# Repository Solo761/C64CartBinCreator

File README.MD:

# C64 Cartridge Creator tool

This is small utility written in Java (1.8) for converting C64 prg files to BIN files for burning to (E)EPROM chips, of up to 64 kB.

## More info

You can choose from three types of cartidges, *Magic Desk*, *Hucky* and *Inverted Hucky*. You can also choose between two types of C64 loaders for these files. First one is loader from Frank Buß' prg2crt python script that can be found [here](http://www.frank-buss.de/c64/prg2crt/index.html), used here with his permission, and the other is loader from C64 tool 152blks.prg that can be used on real C64 (or emulator like Vice) to convert prg files from PRG to *Hucky* type bin files. Now it can be used to also make *Magic Desk* and *Inverted Hucky* type bin files.

From what I've tested both loaders work fine, main difference is that prg2crt loader takes less space, but it doesn't "hide" loading and processing from the screen. 152blks loader uses more space for itself, but it blacks the screen so while it loads from the cartridge you don't see anything happening. So to each to his own.

Beside bin files it can also create CRT for use (or testing) with emulators. With exception of *Hucky* cartridges which aren't supported in CRT file format (at least yet). If you choose combination of Hucky and CRT files tool will warn you about this and ask if you want to abort or continue to create *Inverted Hucky* (also called *RGCD*) CRT instead. 
Basically, difference between *Hucky* and *Inverted Hucky* is order of memory banks, everything else is the same.

## GUI Usage

Basically just start jar file. Either from command line

`java -jar cartCreator.jar`

or just double click jar file from windows, on my PC (Win 10) it automatically starts the tool.

Tool should also work on other OS' that have Java, I tried to avoid OS specific stuff in the code.

## Command Line usage

Tool also supports command line usage, enter 

`java -jar cartCreator.jar -h`

in command line to see help

- Parameters:
	-  **-i \<input file\>** -prg file to convert`
	-  **-t \<cartidge type\>**	- which cartridge type to convert to
		- Cartridge types:
			- **h** - Hucky 64kB
			- **ih** - inverted Hucky 64kB
			- **md** - MagicDesk 64kB
	- **-l \<loader type\>** - which loader to use
		 - Loader types:
			- **a** - prg2crt loader from Frank Buß' python script
			- **b** - 152Blks loader

- Semioptional (you need at least one of them):
	- **-c** - convert to emulation cartridge format (CRT)
	- **-b** - convert to bin file for burning to (E)EPROM

- Optional:
	 - **-o \<output file\>** - output file to save converted file to, if it differs from input file
	- **-h** - help

Order of parameters is not important.

For example:

Convert prg to inverted hucky bin file using "a" variant loader

`java -jar cartConv.jar -i BubbleBobble.prg -t ih -b -l a`

Convert prg to MagicDesk CRT file for use in emulator (e.g. Vice) and bin file using "b" variant loader

`java -jar cartConv.jar -i BubbleBobble.prg -o BubbleBobbleEmu.crt -t md -l b -c -b`

## Additional stuff

In folder *EagleSchematics* are two PCB schematics and designs that can be opened with Eagle PCB, one for MagicDesk compatible cartridge and the other for Hucky/Inverted Hucky cartridge (how you solder three bridges on PCB selects if it's going to work as Inverted Hucky or normal Hucky board.

There are also gerber files for both of them if you want to order them from some PCB manufacturer. If they don't require some special settings these should do, if not you can load schematics/design files to Eagle and make gerber files with their settings.

So far they're untested, I've made one Hucky board DIY with above schematics and it works. I also have both boards made from above gerber files, but so far haven't tried them, I've been busy making this tool :).

MagicDesk board should support up to **256 kB (E)EPROM chips**, but can create only up to 64 kB images. Or more simply said, it needs to fit in C64 RAM, basically any game that could be ran from the tape. 
While it could create BIN/CRT files from bigger PRG files they wouldn't be able to start as they wouldn't fit in C64 RAM.
But you can use [Magic Desk Compatible Cartridge Generator tool](http://csdb.dk/release/?id=132937) from C64 Scene Database to create multi game/application cartridges to fill those 256 kB. My goal for this was to make one cartridge - one game so I didn't dig deeper into it.

**Hucky/Inverted Hucky** 

**MagicDesk**

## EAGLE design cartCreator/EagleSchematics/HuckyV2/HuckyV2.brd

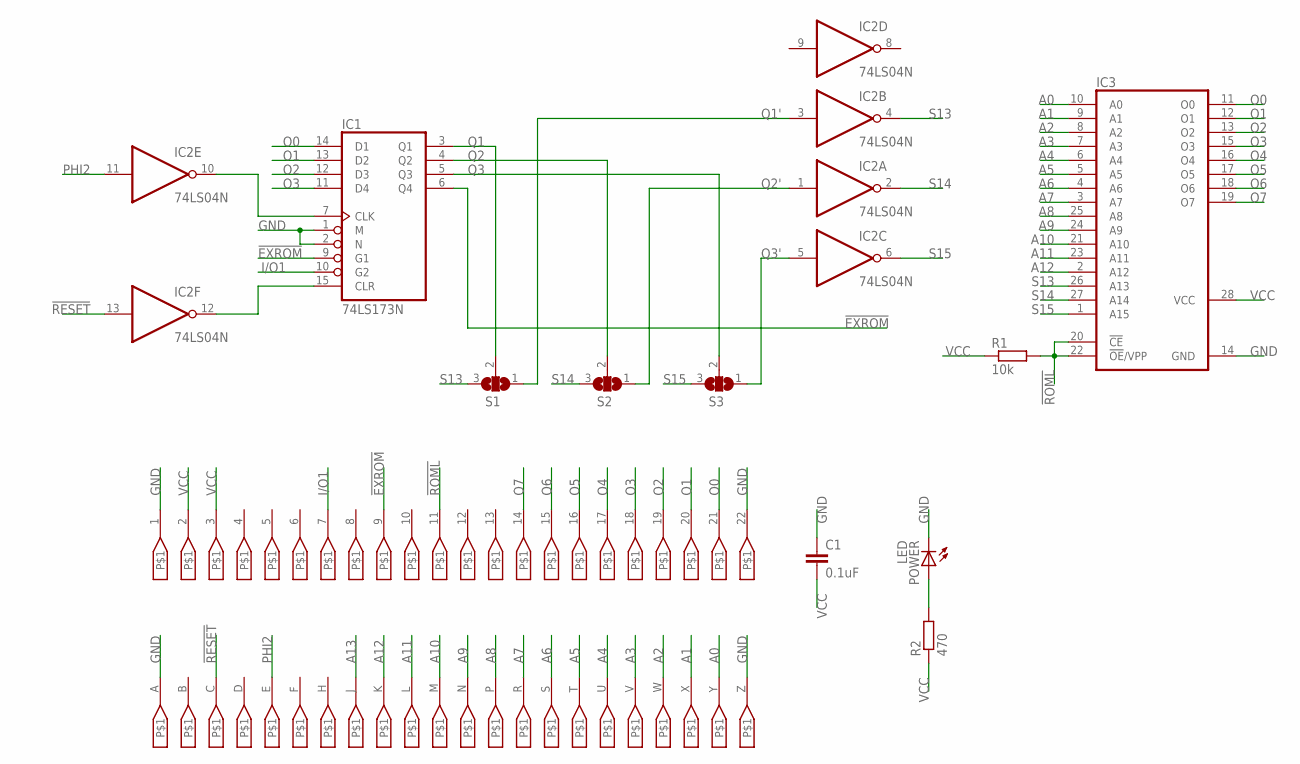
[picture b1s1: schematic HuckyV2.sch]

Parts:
C1: 0.1uF; C050-24X044_SP
IC1: 74LS173N; DIL16
IC2: 74LS04N; DIL14
IC3: 27C512D; DIL28-6
POWER: LED; LED3MM_SMALLER_DRILL
R1: 10k; 0207/10_SP
R2: 470; 0207/10_SP
S1, S2, S3: SJ2W_NUMBERED; SJ_2_NUM
U$1: C64_EXPANSION_FINGERS_PIN8X1.9; C64_EXPANSION_FINGERS_THINNER

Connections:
!EXROM: IC1.6 (Q4), IC1.9 (G1), U$1.9
!RESET: IC2.13 (I), U$1.C
!ROML: IC3.20 (!CE), IC3.22 (!OE!/VPP), R1.2, U$1.11
A0: IC3.10 (A0), U$1.Y
A1: IC3.9 (A1), U$1.X
A2: IC3.8 (A2), U$1.W
A3: IC3.7 (A3), U$1.V
A4: IC3.6 (A4), U$1.U
A5: IC3.5 (A5), U$1.T
A6: IC3.4 (A6), U$1.S
A7: IC3.3 (A7), U$1.R
A8: IC3.25 (A8), U$1.P
A9: IC3.24 (A9), U$1.N
A10: IC3.21 (A10), U$1.M
A11: IC3.23 (A11), U$1.L
A12: IC3.2 (A12), U$1.K
A13: U$1.J
GND: C1.1, IC1.1 (M), IC1.2 (N), IC1.8 (GND), IC2.7 (GND), IC3.14 (GND), POWER.K (C), U$1.1, U$1.22, U$1.A, U$1.Z
I/O1: IC1.10 (G2), U$1.7
unnamed: IC1.7 (CLK), IC2.10 (O)
unnamed: IC1.15 (CLR), IC2.12 (O)
unnamed: POWER.A, R2.2
O0: IC1.14 (D1), IC3.11 (O0), U$1.21
O1: IC1.13 (D2), IC3.12 (O1), U$1.20
O2: IC1.12 (D3), IC3.13 (O2), U$1.19
O3: IC1.11 (D4), IC3.15 (O3), U$1.18
O4: IC3.16 (O4), U$1.17
O5: IC3.17 (O5), U$1.16
O6: IC3.18 (O6), U$1.15
O7: IC3.19 (O7), U$1.14
PHI2: IC2.11 (I), U$1.E
Q1: IC1.3 (Q1), S1.2
Q1': IC2.3 (I), S1.1
Q2: IC1.4 (Q2), S2.2
Q2': IC2.1 (I), S2.1
Q3: IC1.5 (Q3), S3.2
Q3': IC2.5 (I), S3.1
S13: IC2.4 (O), IC3.26 (A13), S1.3
S14: IC2.2 (O), IC3.27 (A14), S2.3
S15: IC2.6 (O), IC3.1 (A15), S3.3
VCC: C1.2, IC1.16 (VCC), IC2.14 (VCC), IC3.28 (VCC), R1.1, R2.1, U$1.2, U$1.3

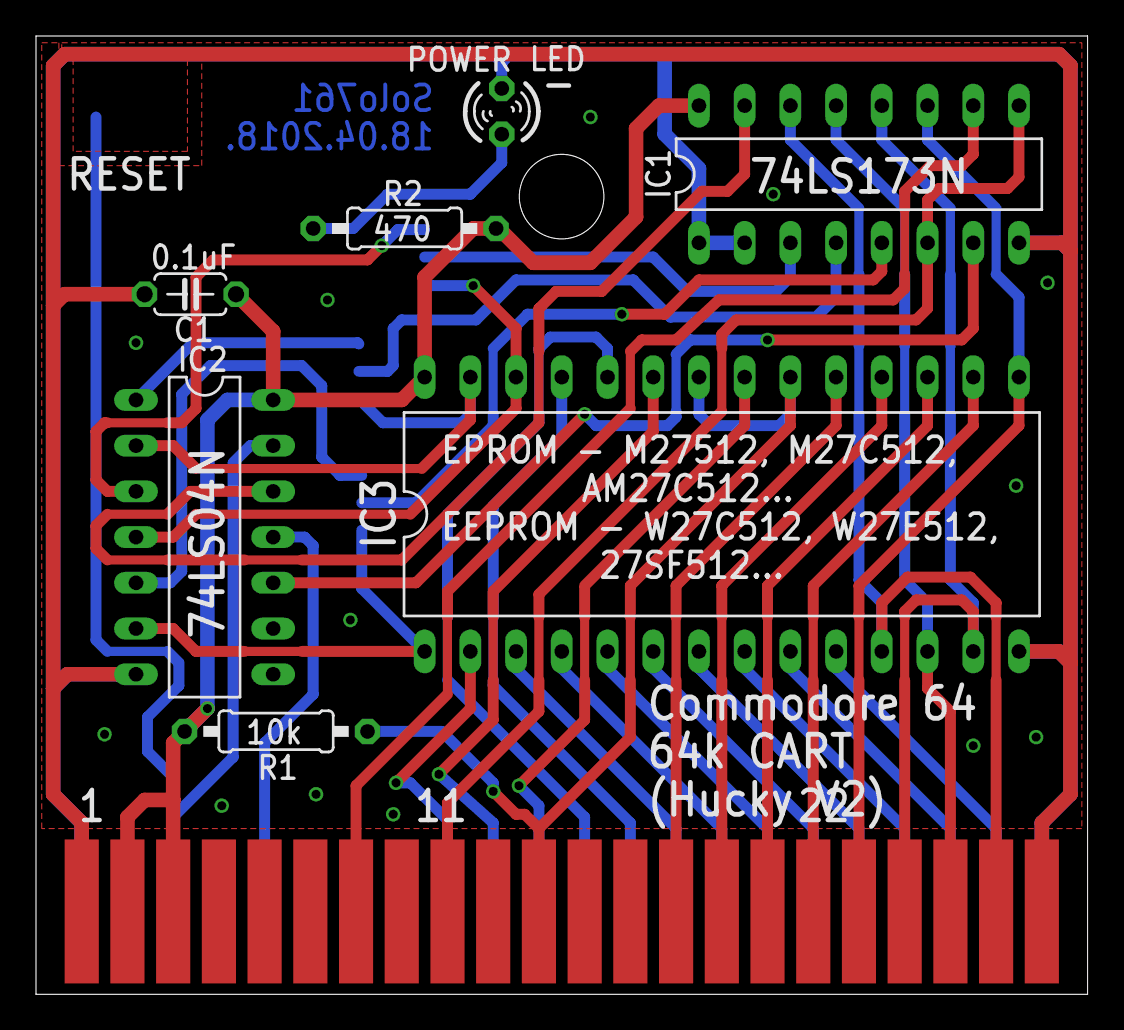
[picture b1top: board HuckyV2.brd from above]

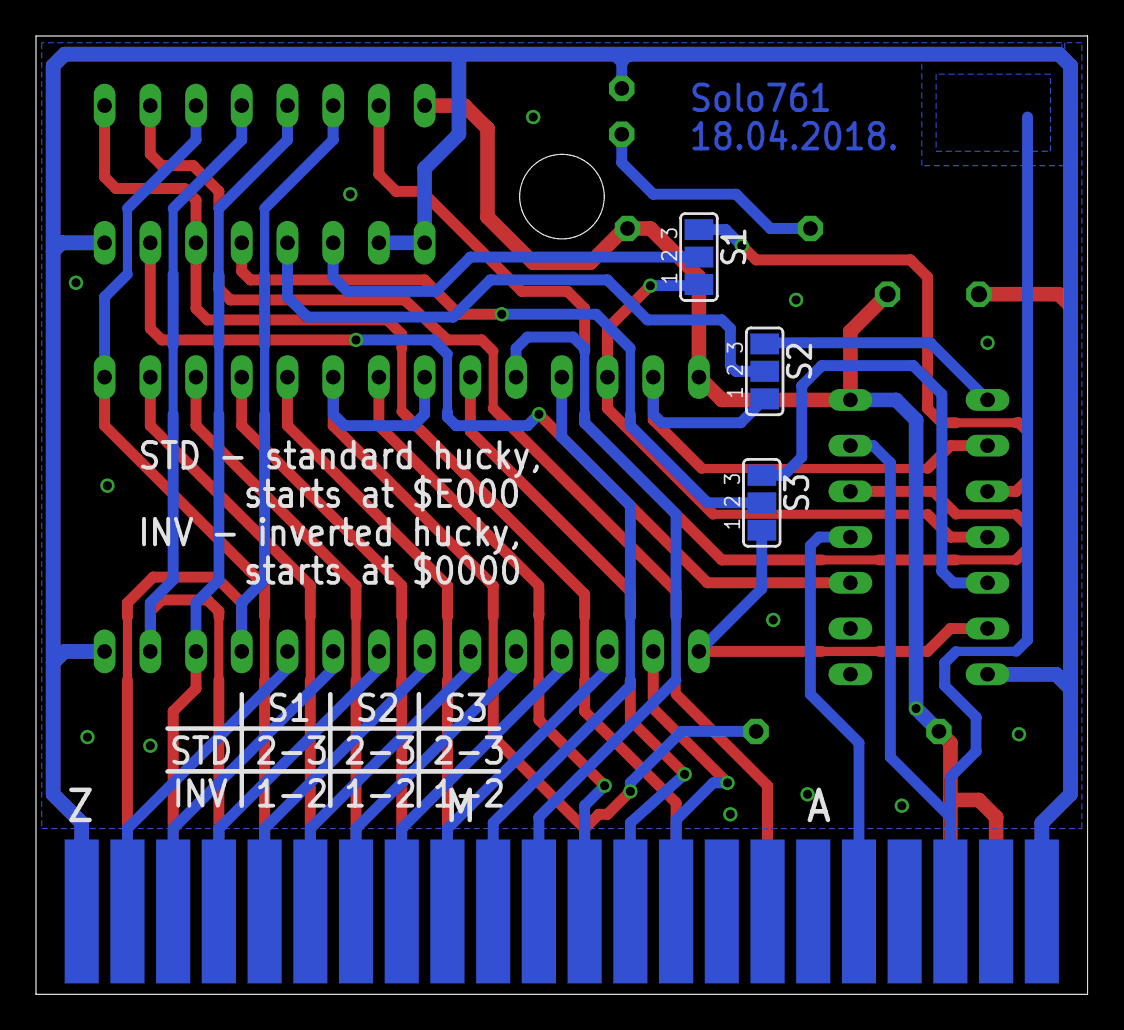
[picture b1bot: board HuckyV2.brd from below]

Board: 2 copper layers, 58.4 x 53.2 mm, 12 parts (3 on the bottom side), 40 nets.

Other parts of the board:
U$2: COMMODORE_SIGN

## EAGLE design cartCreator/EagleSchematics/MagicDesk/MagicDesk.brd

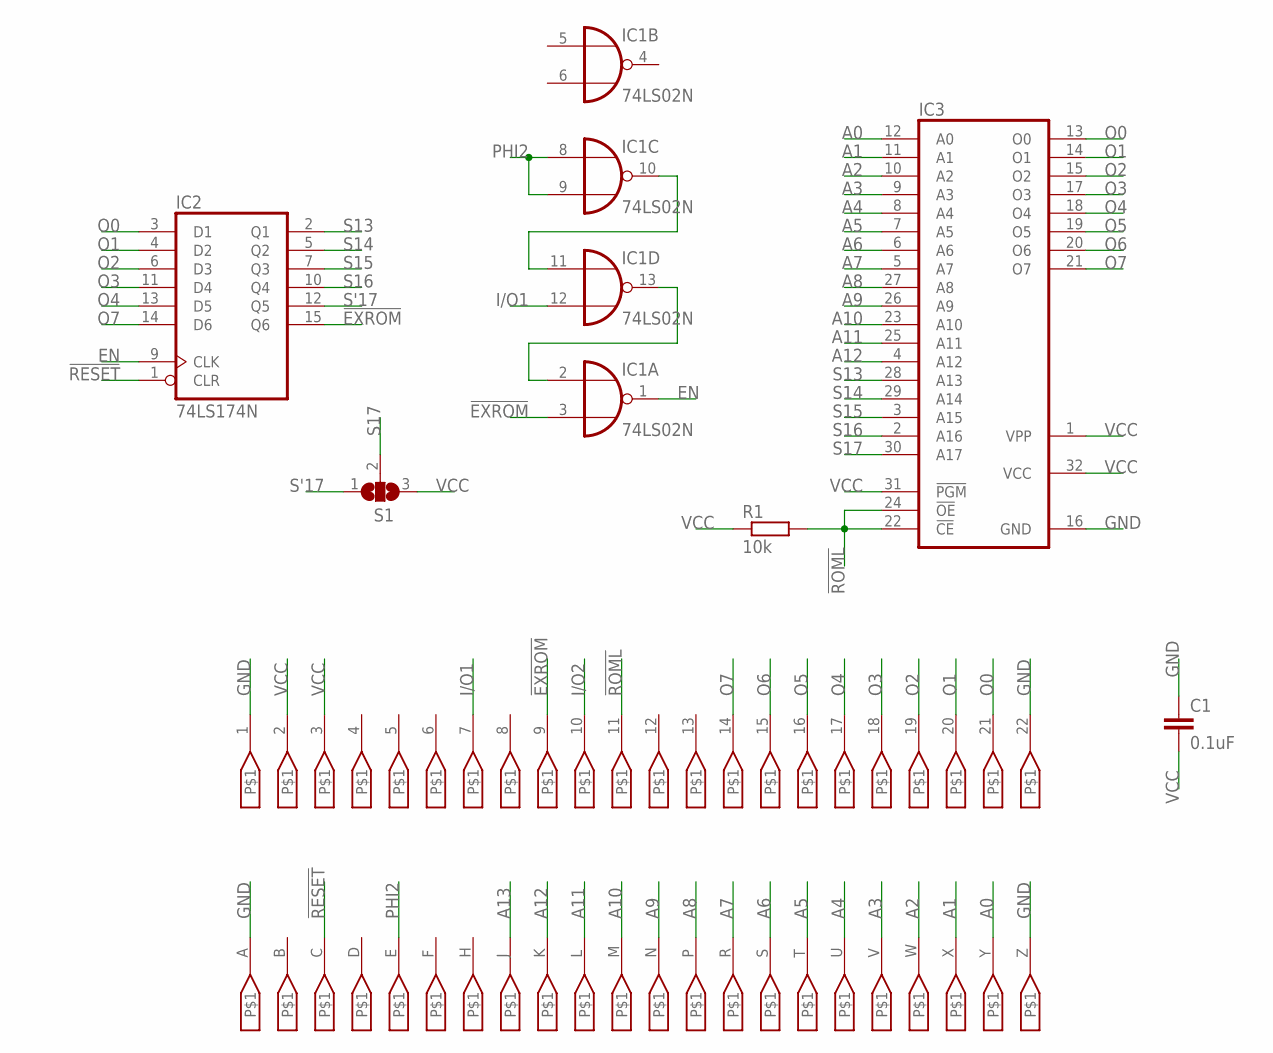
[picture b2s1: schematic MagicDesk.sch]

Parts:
C1: 0.1uF; C050-24X044_SP
IC1: 74LS02N; DIL14
IC2: 74LS174N; DIL16
IC3: 27C2001D; DIL32
R1: 10k; 0207/10_SP
S1: SJ2W_NUMBERED; SJ_2_NUM
U$1: C64_EXPANSION_FINGERS_PIN8X1.9; C64_EXPANSION_FINGERS_THINNER

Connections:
!EXROM: IC1.3 (I1), IC2.15 (Q6), U$1.9
!RESET: IC2.1 (CLR), U$1.C
!ROML: IC3.22 (!CE), IC3.24 (!OE), R1.2, U$1.11
A0: IC3.12 (A0), U$1.Y
A1: IC3.11 (A1), U$1.X
A2: IC3.10 (A2), U$1.W
A3: IC3.9 (A3), U$1.V
A4: IC3.8 (A4), U$1.U
A5: IC3.7 (A5), U$1.T
A6: IC3.6 (A6), U$1.S
A7: IC3.5 (A7), U$1.R
A8: IC3.27 (A8), U$1.P
A9: IC3.26 (A9), U$1.N
A10: IC3.23 (A10), U$1.M
A11: IC3.25 (A11), U$1.L
A12: IC3.4 (A12), U$1.K
A13: U$1.J
EN: IC1.1 (O), IC2.9 (CLK)
GND: C1.1, IC1.7 (GND), IC2.8 (GND), IC3.16 (GND), U$1.1, U$1.22, U$1.A, U$1.Z
I/O1: IC1.12 (I1), U$1.7
I/O2: U$1.10
unnamed: IC1.2 (I0), IC1.13 (O)
unnamed: IC1.10 (O), IC1.11 (I0)
O0: IC2.3 (D1), IC3.13 (O0), U$1.21
O1: IC2.4 (D2), IC3.14 (O1), U$1.20
O2: IC2.6 (D3), IC3.15 (O2), U$1.19
O3: IC2.11 (D4), IC3.17 (O3), U$1.18
O4: IC2.13 (D5), IC3.18 (O4), U$1.17
O5: IC3.19 (O5), U$1.16
O6: IC3.20 (O6), U$1.15
O7: IC2.14 (D6), IC3.21 (O7), U$1.14
PHI2: IC1.8 (I0), IC1.9 (I1), U$1.E
S13: IC2.2 (Q1), IC3.28 (A13)
S14: IC2.5 (Q2), IC3.29 (A14)
S15: IC2.7 (Q3), IC3.3 (A15)
S16: IC2.10 (Q4), IC3.2 (A16)
S17: IC3.30 (A17), S1.2
S'17: IC2.12 (Q5), S1.1
VCC: C1.2, IC1.14 (VCC), IC2.16 (VCC), IC3.1 (VPP), IC3.31 (!PGM), IC3.32 (VCC), R1.1, S1.3, U$1.2, U$1.3

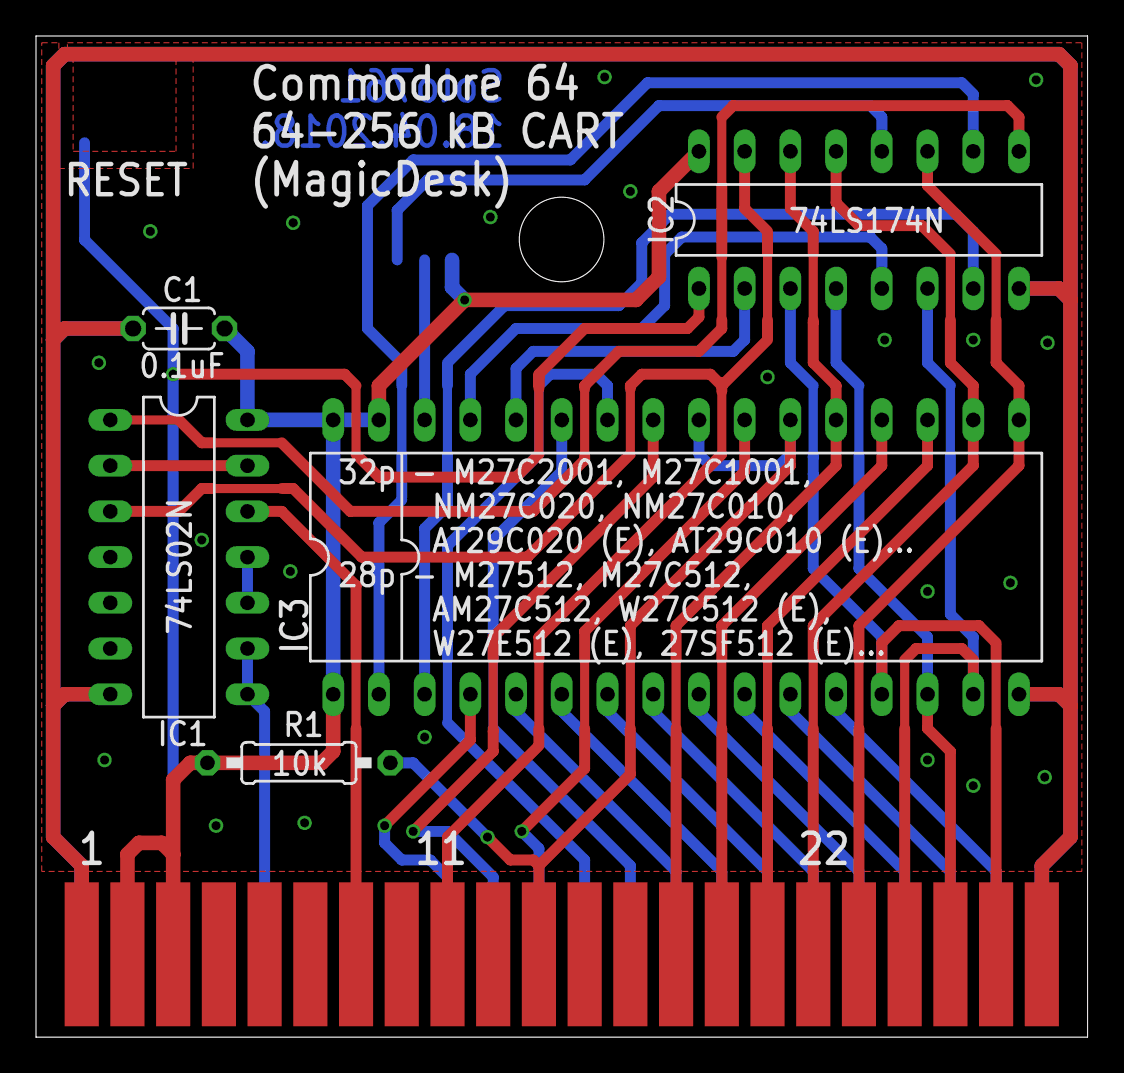
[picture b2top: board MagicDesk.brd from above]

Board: 2 copper layers, 58.4 x 55.6 mm, 8 parts (1 on the bottom side), 37 nets.

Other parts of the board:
U$2: COMMODORE_SIGN

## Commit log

2018-03-27 Basic methods added for inverted hucky bin type
2018-03-31 Refactoring
2018-04-04 Added CRT generation
2018-04-04 Refactoring and version update
2018-04-07 Mostly completed command line version for Inverted Hucky and MagicDesk 64 files
2018-04-10 Added GUI window and some controls
2018-04-10 Added prevention of adding multiples of the same file
2018-04-13 working version
2018-04-14 Set width/heights programmatically through stage settings
2018-04-14 Cmd arguments parser refactorin
2018-04-15 Refactoring and ready for first working version
    - two supported cart types (inverted hucky and magicdesk)
2018-04-15 Small refactor of byte arrays
2018-04-19 Added support for 152blks loader and another refactoring
2018-04-20 Added icon, refactoring, version change
2018-04-20 Upload files to ''
2018-04-20 Update 'README.MD'
2018-04-20 Name update
2018-04-20 JUnit clean
2018-04-21 Schematics and readme update
2018-04-21 Readme fix
2018-04-21 Readme fix 2
2018-04-21 Comment added
2018-04-22 Some error handling added
2018-04-22 Another refactor
2020-10-14 Pom security update
2023-11-29 Bump ch.qos.logback:logback-classic from 1.2.3 to 1.3.12 in /cartCreator
    Bumps [ch.qos.logback:logback-classic](https://github.com/qos-ch/logback) from 1.2.3 to 1.3.12.
    - [Commits](https://github.com/qos-ch/logback/compare/v_1.2.3...v_1.3.12)
    ---
    updated-dependencies:
    - dependency-name: ch.qos.logback:logback-classic
    dependency-type: direct:production
2023-12-05 Bump ch.qos.logback:logback-classic from 1.2.3 to 1.2.13 in /cartCreator
    Bumps [ch.qos.logback:logback-classic](https://github.com/qos-ch/logback) from 1.2.3 to 1.2.13.
    - [Commits](https://github.com/qos-ch/logback/compare/v_1.2.3...v_1.2.13)
    ---
    updated-dependencies:
    - dependency-name: ch.qos.logback:logback-classic
    dependency-type: direct:production
